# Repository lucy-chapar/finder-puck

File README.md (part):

# Finder Puck

A pocket puck so two people can find each other in a loud, crowded place without phones. Each puck has GPS, a
compass and a LoRa radio (915 MHz, no cell service needed); the two swap positions and each shows a **radar-style
arrow and the distance** to the other on a round screen. A vibration motor pulses faster as you get closer, four
LEDs on the face strobe a "beacon me" pattern for the last few metres, and there is exactly one button.

76.4 mm across, 18.3 mm thick. The body is a CNC-machined 6061 aluminium shell, black anodised, under a matte black
plastic face; between 12 and 3 o'clock the side wall is a black plastic antenna window, because aluminium would
block the radios (see [Aluminium shell and the radios](#aluminium-shell-and-the-radios)). Orange anodised
socket-cap bolts on the face pass through the PCB, a 10 mm orange button at 6 o'clock, a clear bezel around the
crystal that the four beacon LEDs light from below, and an orange index dot at 12 o'clock over the GPS patch, which
looks through a 0.9 mm skin. The back is plain anodised aluminium with the Open Source Hardware logo engraved as a
V-groove line through to bare metal; the cord goes in at the side at 6 o'clock and out of the back. The case is designed to IP55 (dust protected, water
jets from any direction) with the USB-C door slid shut and the switch plug pushed home; see [Sealing (IP55)](#sealing-ip55).
[Build guide (PDF)](docs/finder_puck_build_guide.pdf).

## Files

| Path | Contents |
|---|---|
| `finder_puck.kicad_pro` | KiCad 7 project (open this) |
| `finder_puck.kicad_sch` | Schematic ([PDF](docs/schematic.pdf)) |
| `finder_puck.kicad_pcb` | Routed 72 mm round 4-layer board (one edge notch for the battery lead) |
| `lib/finder_puck.kicad_sym`, `lib/finder_puck.pretty` | Project symbols and the 0.7 mm FPC solder footprint |
| `lib/3dmodels/` | 3D models (see "3D models" below) |
| `fab/finder_puck_gerbers.zip` | Gerbers and drill files |
| `fab/finder_puck_bom.csv`, `fab/finder_puck_cpl.csv` | Assembly BOM and placement (JLCPCB column names) |
| `mech/finder_puck.step`, `mech/finder_puck_features.json` | Populated board in 3D, and everything the case needs from it |
| `case/finder_puck_case.FCStd` | FreeCAD assembly: board, panel, crystal, battery, motor, antenna, bolts, shell, window, plate, ring, bezel, cap |
| `case/finder_puck_case.step` | All made parts in STEP |
| `case/finder_puck_{shell,window}_shop.step`, `case/finder_puck_shell_drawing.pdf` | For the shop: the shell and the window each on its own, origin on the axis at the back face, and the shell's A3 drawing (threads, tolerances, finish, setups) |
| `case/finder_puck_{window,plate,ring,bezel,cap}.stl` | Print files (`finder_puck_shell.stl` too, for previews) |
| `case/finder_puck_logo_vgroove.svg`, `case/oshw_logo.svg` | 1:1 drawing of the back logo's V-groove path for the machinist; the logo's source path (Simple Icons, CC0) |
| `case/finder_puck_gaskets.svg`, `case/finder_puck_gaskets.dxf` | 1:1 cutting template for the lid, crystal and door gaskets; the same plus the seam seal and window strip as a DXF for a converter's cutter (a layer per foam thickness) |
| `case/finder_puck_{door,switchplug}.stl` | The sliding USB-C door and the TPU switch plug |
| `docs/finder_puck_build_guide.pdf` | Step-by-step assembly guide (IKEA style) |
| `manual/` | The guide's content, renderer and layout scripts |
| `docs/finder_puck_render{,_pair,_back}.png` | Blender studio renders: the puck searching, the pair that found each other (beacons lit), the back |
| `case/export_meshes.py`, `case/render_blender.py` | Mesh export from the FreeCAD assembly, and the Blender scene behind the renders (see "Renders" below) |
| `tools/`, `case/build_case.py`, `case/render_case.py`, `regen.sh` | Generators for all of the above |
| `firmware/` | ESP32-S3 firmware (PlatformIO); see [firmware/README.md](firmware/README.md) |

## Parts

| Ref | Part | Job |
|---|---|---|
| U1 | ESP32-S3-WROOM-1-N8 | Brain; flashed over USB-C (native USB) |
| U2 | RFM95W-915S2 (SX1276) + U.FL (J4) | LoRa link between the two pucks; the feed is a single pre-routed top-layer track |
| U3 | u-blox SAM-M10Q | GPS with built-in patch antenna, under the sky window |
| U4, U5 | LIS3DH + LIS2MDL | Tilt-compensated compass |
| J3 | 1.28″ 240×240 GC9A01 round IPS panel | The radar screen (bare panel, 12-pin 0.7 mm FPC soldered to the board) |
| Q2, R13–R15 | Backlight driver | Two parallel white LEDs from the battery rail, PWM dimmed |
| LED1–LED4 | WS2812B-2020 | Beacon, up four light pipes into the translucent bezel |
| J5, Q1, D1 | Coin vibration motor and driver | Haptic pulse |
| U6, U7 | MCP73831 charger, AP2112K 3.3 V regulator | 1S LiPo on J2, charged from USB-C |
| SW1 | C&K PTS645 (5 mm stem), under the orange cap | Beacon / pair button |
| SW2, Q3, R22 | C&K PCM12 slide switch, AO3401A | On/off: the switch grounds the P-FET's gate, the FET carries the current |
| H1–H4 | M2.5 plated holes | The four case bolts pass through them |
| H5 | 2.5 mm hole | Motor lead comes up through the board |
| R21, R25, R26 | Dividers | Charger state and USB-present sensing, scaled to 3 V |
| TP1, TP2 | Test pads | UART0 TX/RX, reachable with the plate off |

ESP32 pins: LoRa SPI on IO10–IO14 (NSS, MOSI, SCK, MISO, RST), DIO0/DIO1 on IO4/IO5. GPS UART on IO17 (to GPS)
and IO18 (from GPS). I2C on IO8 (SDA) / IO9 (SCL) for LIS3DH (0x18) and LIS2MDL (0x1E). **Display on its own SPI
bus: SCK IO40, MOSI IO41, CS IO42, D/C IO21, RST IO47, backlight PWM IO48.** LEDs IO38 (through 220 Ω), motor
IO7 (IO39 has a pull-up at reset and would run the motor during boot), button IO0, battery sense IO1 (half of
VSYS), LIS3DH INT1 IO2, charger state IO6 (high only when the cell is full), USB present IO15.

The panel's FPC pinout (1–12): GND, LEDK, LEDA, VDD, GND, GND, D/C, CS, SCL, SDA, RESET, GND. Run the display at
40–80 MHz (never 26.67 or 13.33 MHz: a harmonic lands on GPS L1).

## How it goes together

Z = 0 is the top of the PCB.

- **Shell** (6061-T6, black anodised): machined in three setups, from the top, the back and the side, with no
  undercuts. A 1.8 mm floor, a bay for a 503450-class LiPo (34.5 × 52 × 5.3 mm, on 0.5 mm foam) whose wall is a
  Ø68.8 bore under the board's Ø72.8 one, so the step between them is the 2 mm ledge the board rests on; four
  Ø6.5 bosses with tapped M2.5 holes (5 mm of thread, blind) that run into the bay's wall with 1.5 mm inside radii
  (a 3 mm cutter); a pocket for the 10 mm coin motor at 2 o'clock; a slot in the bay wall at 304° for the battery
  lead and the antenna pigtail (floor to ledge, out to the board's bore, 1.5 mm inside radii); and the switch slot (1 mm corner radii) with its finger scallop (2 mm radii) and the
  switch plug's Ø1.6 pin hole, all below the rim, so the seam seal passes over them unbroken. Between 12 and 3
  o'clock (−14° to 81° at the floor) the wall is cut down to the floor for the antenna window, and the cut's two
  ends are 60° flanks, so the window gasket on them is squeezed by the bolts like the rim seal is; the boss at 45°
  stands on its own there, and the one at 315° stays whole outside it. Two Ø2.1 holes in that floor take the window's pegs. The outer edge of the back has a
  1 mm radius. The back is plain apart from the Open Source Hardware logo, 22 mm across, engraved as a line: a 90°
  V-bit follows its outline (a contour, not a pocket) 0.3 mm deep, so the groove is 0.6 mm wide, after anodising so
  it shows bare aluminium (`case/finder_puck_logo_vgroove.svg` is the 1:1 drawing). The lanyard is two Ø3.0 holes drilled square to the
  surface at 6 o'clock, one up from the back (r 35.3, stopping 1 mm above the side hole's axis, so its point stays
  0.7 mm under the boss's top) and one in from the side (Z −6.2), meeting in a boss inside the wall, with 0.4 mm countersinks on both mouths; deburr the inside of the bend.
- **Window** (black, printed): the plastic wall that fills the shell's notch, 0.6 mm clear of the notch floor and
  both flanks (normal to each face: the window gasket's squeeze), flush with the shell's rim at the top. It carries
  the 915 MHz flex antenna on its inside, the USB-C opening up to the parting line, the door's pocket with its
  sealing land and lower groove, and two feet inside the wall that stand on the shell's floor with Ø2 pegs in its
  holes, which locate it and set the gasket's squeeze.
- **Board** sits on the ledge (the 2 mm step between the two bores, cut away in the window); the motor lead comes up through H5 next to J5,
  and the battery lead and the antenna pigtail come up through a 4.5 mm notch in the board edge at 304°. J2 sits
  5.6 mm from the wall so the PH plug fits in front of it.
- **Ring** (black): a short cup standing on the board on a 0.5 mm foam ring. Its 0.85 mm wall (Ø36.3 bore,
  0.35 mm around the panel) is open at 6 o'clock where the panel's chin and the folded FPC pass, and starts
  3.6 mm up over the ESP32 can. The panel drops in from above onto the ledge 4.0 mm above the board. The ring
  is modelled 0.25 mm into the foam, so the bolted stack always preloads it. Over the GPS module (64–116°) the
  wall is a single 0.45 mm perimeter (outer face at r 18.6), 0.6 mm from the module at its widest: the SAM-M10Q
  data sheet (UBX-22013293, table 19) gives 15.4–15.6 mm over the whole height, 5.8–6.8 mm tall, with
  de-paneling tabs of up to 0.3 mm at the PCB corners. u-blox's own STEP draws the patch 0.5 mm narrower than
  the drawing does, so the drawing is what the case is built to.
- **Bezel** (clear resin): a 0.3 mm foam gasket sits on the panel's glass, the Ø37.5 × 1.0 mm flat mineral
  crystal rests on the ring's top, and the bezel sits over both: a skirt around the ring top locates it (0.25 mm
  radial), its seat holds the crystal (0.25 mm radial), its lip (Ø34.8 window, flared to Ø43.4) overlaps the
  glass by 0.2 mm and is the visible dial ring, pressing a 0.3 mm die-cut foam ring (Ø35.2–37.2) onto the
  crystal's edge, and its 0.5 mm flange under the plate skin, which runs all the way round, is what the bolts
  clamp, through a die-cut lid gasket. The flange has a lobe at 6 o'clock that carries the button bore's sleeve
  (down to Z 5.2, with a 0.4 mm lead-in, for the cap's O-ring) and a tab out to the charge LED with a Ø1.2 mm
  light pipe up through the skin to the face (Ø1.6 below the flange, 0.3 mm above the LED). Four Ø3 mm light
  pipes hang from the flange to 0.3 mm above the WS2812s, so the whole lip glows when the beacon runs. Over the
  GPS module (12 o'clock, 64–116°) the ring wall is thinned and nothing of the bezel beyond r 18.7 comes below
  the flange (Z 7.0, 0.2 mm over the tallest module). The ring used to be one part; a panel cannot be fitted past a ledge below it and a lip above it, hence the split. `LIP_PROUD`
  raises the lip's top above the face (default 0, see "Seeing the beacon from the side").
- **Plate** (black): plastic on purpose, since it is the GPS patch's radome. Skin 1.6 mm, face at Z 8.6, Ø8 bosses
  down to the board (they, not the rim, are the datum: the 1.8 mm skirt stops 0.6 mm above the rim of the shell and
  the window, the gap the 1.0 mm foam seal is squeezed into), Ø5.2
  counterbores so the orange M2.5 × 12 socket-cap heads sit 0.2 mm proud on a 0.5 mm nylon washer (Ø3.0 bores,
  Ø2.8 holes in the board), the Ø44 bezel opening (0.3 mm reveal) with a pocket 0.7 mm deep under
  the skin for the bezel's flange and the lid gasket, the skin thinned to 0.9 mm over the GPS module out to the
  wall (`GPS_WINDOW = "open"` in `build_case.py` cuts it open instead), a blind Ø1.8 × 0.6 mm hole in that cover
  at 12 o'clock for a glued orange 1.75 mm filament stub, the Ø10.6 button bore (the bezel's sleeve continues
  it), a Ø1.4 bore for the charge-LED pipe, a 1.2 mm dimple beside the switch slot marking its ON end (towards 9 o'clock, away from the
  button: the PCM12 closes terminals 1–2 with the knob at the terminal-1 end, and terminal 1 is the grounded
  one), and the 13.5 × 7.5 mm USB-C opening shared with the window at the parting line.
- **Cap** (orange): Ø10, 1.5 mm proud, 1.0 mm edge radius, a Ø12.4 flange captive 0.1 mm under the bezel's
  sleeve (so the cap goes on before the bezel), a
  groove for a 9 × 1 mm silicone O-ring that seals against the sleeve's bore (0.8 mm gland, 20 % squeeze;
  the groove's upper wall is 45° so it prints pocket down), and a square pocket that sits on the PTS645 stem
  (a dot of glue keeps it there).
- **USB-C door** (black): a 0.6 mm curved door, 16.7 mm wide, that slides 24.5° round the window in its pocket,
  flush with the wall (0.05 mm proud, three grip ribs), held by tongues in the two grooves, so it is captive
  once the plate is on. A die-cut 0.5 mm closed-cell foam frame on its inside rides 0.05 mm clear of the pocket
  floor while it slides and is squeezed to 0.3 mm (40 %) on the land when it is shut: a sliding seal that only
  compresses at the end of its travel, so it doesn't drag or wear. It slides open towards 2 o'clock; shut, the pocket's
  clockwise end stops it over the land; open uncovers the whole USB-C plug overmold.
- **Switch plug** (TPU 85A–95A): its body fills the switch slot 0.1 mm oversize, 0.14 mm clear of the knob, its
  flange lies on the scallop floor, with a grip ridge and a strap to a pin glued into the shell. Lift it to
  switch on or off.
- **Bolt path:** head → nylon washer → plate boss → PCB (plated, grounded 5.4 mm pad on both sides) → shell boss,
  tapped M2.5. The bolt engages 4.1 mm of thread (1.6 × its diameter). Hand-tighten only; aluminium hex sockets
  strip, and a smear of grease on the thread stops aluminium galling on aluminium. The bolts and index stub are in
  the FreeCAD model; the threads are modelled at their nominal 2.5 mm, so the bolts show as touching the shell.

`build_case.py` places every opening from the board's feature file and checks the eight made parts (the machined
shell and seven printed parts) against the populated board, panel, crystal, battery, motor, antenna, bolts, washers,
the seam seal, the window gasket, the O-ring, the door, crystal and lid gaskets and each other, and against proxies
for what the board model lacks: the mated battery plug (a 6.85 × 5.8 × 4.5 mm PHR-2 housing standing 2 mm out
of J2's mouth, 2.5 mm from the wall), the two battery wires and the pigtail standing side by side in the
notch, the FPC's 0.45 mm fold bump under the panel chin, a USB-C plug's 12.35 × 6.5 mm overmold and the GPS
module at its data-sheet limits (15.6 mm square, 6.8 mm tall, 0.3 mm de-paneling tabs at the PCB corners). The
result must be 0 interferences. The switch plug's 0.1 mm squeeze into its slot is designed, so it is listed as a
`squeeze` line rather than counted. The closed door is not checked against the cable-overmold proxy, since the
two are never there at once; instead the door is also built slid open and checked against the window, plate, seal
and the overmold (the `door open` lines: no overlap, and more than 1 mm from the overmold). It also lists every made-vs-other pair closer than
0.3 mm with the nearest point (the `gap` lines); today that list is exactly the designed seats and fits and
nothing else. The `rf:` lines give how close the aluminium comes to the antenna and to the GPS module, and the
`window gasket` line the length of foam strip to cut:

| Gap | Pairs |
|---|---|
| contact | board on the shell ledge, motor in its pocket, bolts in the shell's threads (modelled at the nominal diameter), the window's feet on the shell floor, antenna on the window, plate bosses on the board, washers under the bolt heads in the counterbores, the seal between the rim of the shell and window and the plate skirt, the window gasket between the shell and the window, the O-ring in the cap's groove and the bezel's sleeve, the door's gasket between the door and the land, the lid gasket between the bezel flange and the plate, the crystal gasket between the crystal and the lip, panel and crystal on the ring, bezel on the ring top, index stub on the bottom of its hole |
| 0.05 mm | the door in its pocket and its tongues in the grooves, the door over the seal's end, the window's pegs in their holes |
| 0.1 mm | cap flange under the sleeve, cap pocket over the button body, charge-LED pipe in its bore |
| 0.14 mm | switch plug over the switch knob |
| 0.2 mm | bezel over the panel (the compressed gasket), bezel over the crystal (its gasket), bezel flange over the GPS module at its tallest, USB-C plug overmold under the plate |
| 0.25 mm | bolt shanks in the plate bores, ring foot over the board (the compressed foam ring) |
| 0.3 mm | cap in the plate's bore, USB-C plug overmold in the window's opening |

Machine the shell (see "Machining the shell" below). Print the window upside down (its rim on the bed), the ring upside down (top face on the bed; slow the perimeters under its
0.85 mm ledge, and let the slicer print the single-perimeter 0.45 mm wall over the GPS arc as a thin wall), the
plate face down and the cap pocket down, the door standing on its edge, and the switch plug in TPU (85A–95A)
standing on its strap end. The
outer edges on the bed are 45° chamfers. The bezel's flange is a horizontal shelf whichever way up it goes and its fits are 0.25 mm, so
print it in clear resin (SLA); FDM needs supports under the flange and will not make clean light pipes.

### Aluminium shell and the radios

Aluminium blocks both radios, so nothing metal may sit between an antenna and the sky:

- **GPS:** the SAM-M10Q's patch looks up through the plate's 0.9 mm skin, so the plate stays plastic. The shell's
  wall comes within 0.5 mm of the module's corner at 12 o'clock (at the data sheet's limits), but its rim is at
  Z 3.0, 3.4 mm below the top of the patch, so it sits beside the module's ground, not over the patch.
- **LoRa:** the flex antenna moved from the shell's wall to the inside of the plastic window (14°–77°), raised
  2 mm so its lower edge is 2.5 mm above the aluminium floor, with 4 mm of plastic to the flank at its 12 o'clock
  end. The nearest aluminium is the bolt boss at 45°, 1.4 mm inside the antenna (the aluminium bolt and the board's
  ground plane were already about as close in the printed case).
- **Window, not slot:** a 915 MHz wave is 33 cm long; a small plastic window in a metal wall would pass very little,
  so the window is a third of the wall, open above to the plastic plate.

Nothing here has been measured. On the first pucks, compare the LoRa range and the GPS time to first fix
against a puck in the previous revision's all-plastic case (tag it, or check out the commit before this change); if the range is short, try the antenna lower or
higher on the window before anything else.

### Machining the shell

Send the shop `case/finder_puck_shell_shop.step`, `case/finder_puck_shell_drawing.pdf` and
`case/finder_puck_logo_vgroove.svg` (`case/shop_drawing.py` writes the first two from the build); quote it as 6061-T6, Type II black anodise (MIL-A-8625
Type II, class 2, about 10–15 µm), ±0.05 mm on the two bores, the bosses' faces and the flanks, ±0.1 mm elsewhere,
and with these notes:

- Three setups. Top: the two bores, the bay and its bosses, the notch and its flanks, the motor pocket, the cable
  slot, the peg holes, the M2.5 holes (tap drill Ø2.05 × 6 mm, thread 5 mm, 0.3 mm countersink). Back: the 1 mm
  outer radius, the lanyard's back hole, the logo. Side, on a 4th axis or an indexing fixture (two stations 25°
  apart, both radial): the switch slot and scallop and the plug's pin hole at 245°, the lanyard's side hole at 270°.
  Every other face is reachable straight down from the top or straight up from the back.
- The flanks are planes 60° from the floor, each through the radial line at the floor's corner, so a 60° (30° per
  side) chamfer mill on the top setup cuts each one in a single pass along that line, its point in the corner. That
  needs about 11 mm of flute: the notch is 10.9 mm deep. A ball-end 3D pass works too. Break the flanks' sharp
  (60°) edges where they meet the outside and the rim.
- Smallest tool: 2 mm (the switch slot's 1 mm corners); bosses meet the bay wall with 1.5 mm radii, and so do the
  6 mm wide cable slot's corners (a 3 mm cutter, 6.3 mm deep). Wall 1.8 mm, floor 1.8 mm; no undercuts.
- Mask the tapped holes from anodising, or chase the threads after. The seal faces (rim, notch floor, flanks) stay
  anodised: the foam seals as well on the oxide, and masking them would only add cost.
- Engrave the logo after anodising: a V-groove along its outline (contour, not pocket), 90° V-bit, tip 0.3 mm deep
  on the line, 0.6 mm wide at the surface (`case/finder_puck_logo_vgroove.svg`, centred on the case axis,
  12 o'clock up when you look at the back), so it reads as a bare aluminium line. Cut before anodising, it would come
  out black on black.
- Deburr the inside of the lanyard's bend so it does not saw the cord.

### Seeing the beacon from the side

The four WS2812s light the bezel lip from below and the lip is flush with the face, so the beacon only shows
from above ([side view](docs/case-side.png)). Three ways to show it from the side were weighed:

- **Lip standing proud** (`LIP_PROUD` in `build_case.py`, default 0): the lip's top rises 1.5–2 mm above the
  plate, a glowing clear ring visible from every direction, level with the orange cap (also 1.5 mm proud). No
  new part, no change to the board, the plate or the bolt sandwich, and the puck is no taller than it already
  is at the cap. Costs: the glass then sits 3.4 mm instead of 1.9 mm below the lip's top, so the lip's inner
  edge hides the outer 1.2 mm of the active area beyond about 19° off-axis (32° today) unless that edge gets
  a 45° chamfer, which would also catch more light; and the resin lip shares the first hit in a face-down
  drop with the cap. 1.5 mm is enough; 2 mm looks like a crown.
- **Smoke-PETG plate:** a 1.6 mm dark translucent skin would show four faint spots over the LEDs and a halo
  round the opening from above, but the plate's outer wall is 14 mm from the LEDs with the ring, the flange
  and the board in between, so nothing useful reaches the side; and the plate stops being matte black and
  ghosts the inside. Rejected.
- **Translucent band at the parting line** (a clear lap lip, or a sixth part): the same light-path problem
  plus a multi-material print or another part. Rejected.

Recommendation: `LIP_PROUD = 1.5` with the inner edge chamfered, if the beacon should be seen from the side;
the default build keeps the flush lip, so the look the owner chose is unchanged until that one constant is set.

## Sealing (IP55)

IP55 is dust protected (no harmful deposit) and water jets from any direction (IEC 60529: a 6.3 mm nozzle,
12.5 l/min from 2.5–3 m, at least 3 minutes). Every way in from outside ends at one of these:

| Path | Seal |
|---|---|
| Shell-to-plate seam | 1.0 mm closed-cell foam (EPDM, neoprene or PORON), a 1.7 mm wide ring (Ø72.9–76.3) on the rim of the shell and the window under the plate's 1.8 mm skirt, squeezed to 0.6 mm (40 %) by the bolted stack. The plate's bosses stay the datum, so the squeeze does not depend on how hard the bolts are done up. At the door it runs out to the pocket floor and the land, and it is open only across the USB-C opening itself, inside the door's gasket |
| Shell to window | a 1.0 mm closed-cell foam strip, 1.7 mm wide and about 87 mm long, along the notch floor and up both 60° flanks to the rim, where the seam seal's ring runs over its ends; squeezed to 0.6 mm normal to each face. The window's feet stand on the floor, so its squeeze is set by the parts, not by the bolts |
| USB-C opening | Sliding door: a die-cut 0.5 mm closed-cell foam frame on its inside, squeezed 40 % on a raised land round the opening when shut (and clear of the pocket while sliding) |
| Switch slot | TPU plug in the scallop; the slot no longer reaches the seam |
| Button | 9 × 1 mm silicone O-ring on the cap, in the bezel's sleeve (grease it) |
| Bolt bores | DIN 433 M2.5 nylon washer under each head; the tapped holes in the shell are blind |
| Crystal | die-cut 0.3 mm closed-cell foam ring on its edge, squeezed to 0.2 mm under the bezel's lip |
| Bezel to plate | die-cut 0.3 mm closed-cell foam lid gasket on the bezel's flange, squeezed to 0.2 mm under the plate's pocket ceiling. It rings the opening and runs round the button bore (1.5 mm web) and the charge-LED pipe (1.1 mm web), so water down either bore stops at it |
| Charge LED | a light pipe on the bezel, up through the skin: sealed by the lid gasket round it, not by a hole in the plate |
| Index stub | glued into a blind hole, 0.3 mm of skin under it |
| GPS window | the 0.9 mm skin (`GPS_WINDOW = "open"` cuts a hole and is not sealed; the build prints a CHECK) |
| Lanyard hole | two holes meeting in a solid boss, not into the case; the window's peg holes are blind and inside the seal |

Nothing is glued or potted: the lid (plate, bezel, crystal, cap) comes off as one piece with the four bolts, so
the panel stays reachable, and the gaskets are cut again from the 1:1 template `case/finder_puck_gaskets.svg`
(lid and crystal gaskets, and the door's frame flat) when they take a set. The lid gasket and the
0.5 mm foam ring under the ring are squeezed in series by the bolted stack (the plate's bosses fix the total),
so the lid gasket wants a much softer foam than the ring's (see "Sourcing the seals"); a
black crystal gasket shows as a thin dark line through the clear lip, a white or clear one does not. Nothing has been tested yet: the rating is what the design aims at. To check a built puck, put a
dry tissue inside, close it, and spray it from 2.5–3 m with a hose and a 6.3 mm nozzle (a 12.5 l/min flow)
for 3 minutes, turning it to reach every face, then open it; for dust, shake it in a bag of talc. The design
has no pressure vent: a sealed puck that goes from a hot car into cold water pulls a little vacuum, so if
water gets in only after big temperature swings, an adhesive ePTFE vent over a small hole in the floor is the
next step.

### Sourcing the seals

| Seal | Qty | Material | Where |
|---|---|---|---|
| Seam seal, window strip | 1 + 1 | 1.0 mm PORON 4701-15 Soft Seal (made for dust and water gaskets), or 1/32" (0.8 mm) closed-cell neoprene/EPDM sponge with adhesive as a stopgap (25 % squeeze instead of 40 %) | Rogers samples, or a converter (TBP Converting, Stockwell Elastomerics, JBC Technologies) |
| Door frame | 1 | 0.5 mm PORON 4701-30 Very Soft (0.53 mm supported) | converter, as above |
| Crystal gasket | 1 | 0.30 mm PORON 4701-50 Firm-Thin (about 32 psi at 25 %, ±0.08 mm thick) | converter, as above |
| Lid gasket | 1 | 0.3 mm: the softest closed-cell foam a converter has at that thickness, else 4701-50 Firm-Thin; see below | converter, as above |
| Foam ring under the ring (not a seal, but in the lid's force path) | 1 | 0.5 mm PORON 4701-50 Firm (0.51 mm) | converter, as above |
| O-ring | 1 | 9 × 1 mm silicone, 70A (RS PRO 772-044, bag of 50) | RS, TME, any metric O-ring stockist |
| Washers | 4 | DIN 433 M2.5 nylon, 2.7 × 5 × 0.5 mm | Accu, TME, Bossard, Essentra |

Converters cut from `case/finder_puck_gaskets.dxf` with a knife plotter or laser, without tooling; for two or
three pucks, the 1:1 SVG and a sharp blade do too. Adhesive: none on the lid, crystal and seam gaskets, which are
clamped; a thin acrylic PSA on the window strip and the door frame helps assembly.

**The lid stack.** The bezel stands on the ring, so the lid gasket (about 530 mm²) and the 0.5 mm foam ring under
the ring (58 mm²) carry the same bolt force in series, and share the 0.35 mm of squeeze the parts leave them. In
one foam the ring's foam, with a ninth of the area, would take nearly all of it and the lid gasket only about
0.05 mm. So the foam ring is firm PORON 4701-50 (0.51 mm), and the lid gasket is the softest 0.3 mm foam to be had.
No very soft PORON is made that thin, so the lid gasket's squeeze stays small: check it on the first puck (a strip
of paper under the gasket should be held all round once the bolts are in) and in the hose test. A 0.5 mm very soft
lid gasket in a pocket 0.2 mm deeper is the fix if it leaks. The crystal gasket is not in that chain: the crystal
sits on the ring as the bezel does, so its 0.1 mm squeeze is set by the crystal's and the bezel's thickness.

## Renders

Made in Blender 3.5 (Cycles, Metal GPU) from the FreeCAD assembly. `regen.sh` does not run this, because it takes
5 to 13 minutes a view on the M4 (the back view is the slowest):

    MESH_DIR=case/blender_mesh /Applications/FreeCAD.app/Contents/Resources/bin/freecadcmd case/export_meshes.py
    blender -b --python case/render_blender.py -- hero,pair,back 512 2400

These renders predate the aluminium shell (they show the printed case and the old debossed back); `render_blender.py`
already has the anodised shell, the bare V-groove logo, the window and the new cord route, so re-run it. The screen
graphics, the cord and the cord lock exist only in the Blender scene. Each view is also saved as
`case/blender_mesh/finder_puck_<view>.blend` for hand tweaking. The hero's rim light is placed from the camera's
mirror angle off the crystal; move that camera and the light's reflection slides onto the screen.

## 3D models

Real models now cover the parts that used to be boxes:

| Part | Model | Source and licence |
|---|---|---|
| ESP32-S3-WROOM-1 | `ESP32-S3-WROOM-1.step` | KiCad library (gitlab.com/kicad/libraries/kicad-packages3D), CC-BY-SA 4.0 with the KiCad design exception |
| SAM-M8Q/M10Q | `ublox_SAM-M8Q.step` | SparkFun KiCad libraries, CC BY 4.0 (offset to KiCad's footprint); `ref/ublox_SAM_official.step` is u-blox's own geometry for cross-checking |
| USB-C HRO TYPE-C-31-M-12 | `USB_C_Receptacle_HRO_TYPE-C-31-M-12.step` | SparkFun, CC BY 4.0 |
| WS2812B-2020 | `LED_WS2812B-2020_PLCC4_2.0x2.0mm.step` | SparkFun, CC BY 4.0 |
| PTS645 button, U.FL, passives | KiCad 7's own library | shipped with KiCad |
| RFM95W, JST PH, JST SH | generated by `tools/make_models.py` | correct outline and height, plain shapes |

Each model's position was checked by exporting a test board and measuring where the solid lands relative to its
footprint. `make_models.py` refuses to overwrite a real model.

## Checks

- Generator: the schematic netlist is checked pin by pin against the parts list; the board layout is checked for
  parts taller than 3.5 mm under the panel, parts under the folded FPC, and parts under the case bosses.
- Board: DRC must report no violations and 0 unconnected (the generator prints it). The design rules are verified
  after loading; if they are not the project's, the build stops.
- Schematic: run ERC in KiCad (Inspect → Electrical Rules Checker); KiCad 7 has no command-line ERC.
- Case: 0 mm³ interference, printed in `build_case.py`'s output, followed by the `gap` list (every made-vs-other
  pair closer than 0.3 mm, which should be the designed seats and fits only), the `rf:` lines (aluminium to the
  antenna 1.4 mm, to the GPS module 0.5 mm, both beside rather than over them) and a `mesh` line per STL (closed,
  no self-intersections).

## Before ordering

- **Nothing has been built yet.** The firmware in [`firmware/`](firmware) drives the GC9A01 and
  builds, but hasn't run on hardware. Its README lists what still needs checking on a real board.
- **Panel FPC, pin 1:** the board puts pin 1 on the 3 o'clock side after the FPC folds under the glass, derived from
  the panel drawing's front view. Buy two panels first and confirm with a loupe which face carries the contacts
  after the fold and where pin 1 lands; if it is mirrored, flip `FPC_PIN1_RIGHT` in `generate_puck.py` and
  regenerate. The FPC tail (12.24 mm) reaches the pads with about 1 mm to spare at the 4.0 mm panel height.
- **GPS footprint:** the SAM-M10Q sits on KiCad's SAM-M8Q footprint, which u-blox lists as pin-compatible.
  The panel's metal frame is closer to the module than u-blox likes (a few dB of margin); the open window compensates.
- **Battery polarity:** J2 pin 1 is `+`. Many LiPo leads are wired the other way round; check with a meter.
- **Antenna:** an adhesive flex antenna for 915 MHz no larger than 40 × 7 mm with a U.FL pigtail of at least
  100 mm (2J 2JF0515P, 39.9 × 7 mm, fits); it goes on the inside of the plastic window, never on the aluminium. Its
  cable end goes at 3 o'clock and the pigtail runs along the floor to the notch at 304° and up to J4. Always connect it to J4 before the radio transmits.
- **Factory parts:** the RFM95W is not stocked by JLCPCB (consign it or hand-solder it); the SAM-M10Q is
  (C5443880). The BOM's LCSC column is filled for everything else: the named parts, and the passives by value
  and package (Samsung MLCCs and UNI-ROYAL 1 % resistors, checked on jlcpcb.com on 2026-10-20). All are
  JLCPCB basic parts except the 150 kΩ 0402 (C25755) and the 27 Ω 0805 (C17594), which have no basic
  equivalent, and the connectors, LEDs and ICs, which are extended. The CPL adds JLCKicadTools' rotation
  corrections (SOT-23 −90°, USB-C shell 180°, WS2812B-2020 90°, JST PH 180°; its table was checked on
  2026-10-20, and the tool is deprecated in favour of JLCPCB's Fabrication Toolkit, which carries the same
  table). The JST SH (J5) is not in that table: 180° is assumed because KiCad draws both horizontal JST
  footprints the same way, so confirm it in the preview along with pin 1 of every polarised part, especially
  U2–U5. Gerbers, drills and the CPL share the drill/place origin. Order with "min via hole 0.25 mm" and edge rails; tell them the switch knob (2 mm at 245°)
  protrudes past the round outline and that the notch at 304° is intended.
- **Bolts:** M2.5 × 12 socket cap, aluminium (non-magnetic, matters for the compass 7 mm from one of them),
  into M2.5 threads tapped in the aluminium shell (no inserts). Grease the threads.
- **Shell:** machined and anodised to `case/finder_puck_case.step` with the notes in "Machining the shell". Check
  the logo is carved after anodising and the tapped holes and seal faces were masked.
- **Factory assembly:** JLCPCB's preview usually needs part rotations corrected. J3 (the panel) is soldered by
  hand; TP1/TP2 and H1–H5 are not parts. Match parts by the manufacturer numbers in the BOM.
- **Crystal:** Ø37.5 × 1.0 mm flat mineral watch crystal (sold in 0.1 mm steps); it bears on a 0.6 mm land.
- **Battery:** a 503450 cell with 28 AWG leads (the notch and the bay above the cell are sized for that); put a
  0.2 mm PET or Kapton sheet between the cell and the board.

## Shopping list

Everything the puck needs that is not on the JLCPCB-assembled board, for two pucks plus spares. Prices are rough
US dollars per unit or pack as listed on 2026-10-22, before shipping, tax and duty. Stock moves, so check it at
order time. AliExpress and Amazon listings go stale; the first column is the spec to buy against.

**Buy the panels first:** pin 1 has to be checked on a real panel (see "Before ordering") before the boards are
ordered. The rest can be ordered with the boards; the AliExpress lines take longest.

| Part (buy to this spec) | Source | Qty | ~Unit | Lead time | Check when it arrives |
|---|---|---|---|---|---|
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
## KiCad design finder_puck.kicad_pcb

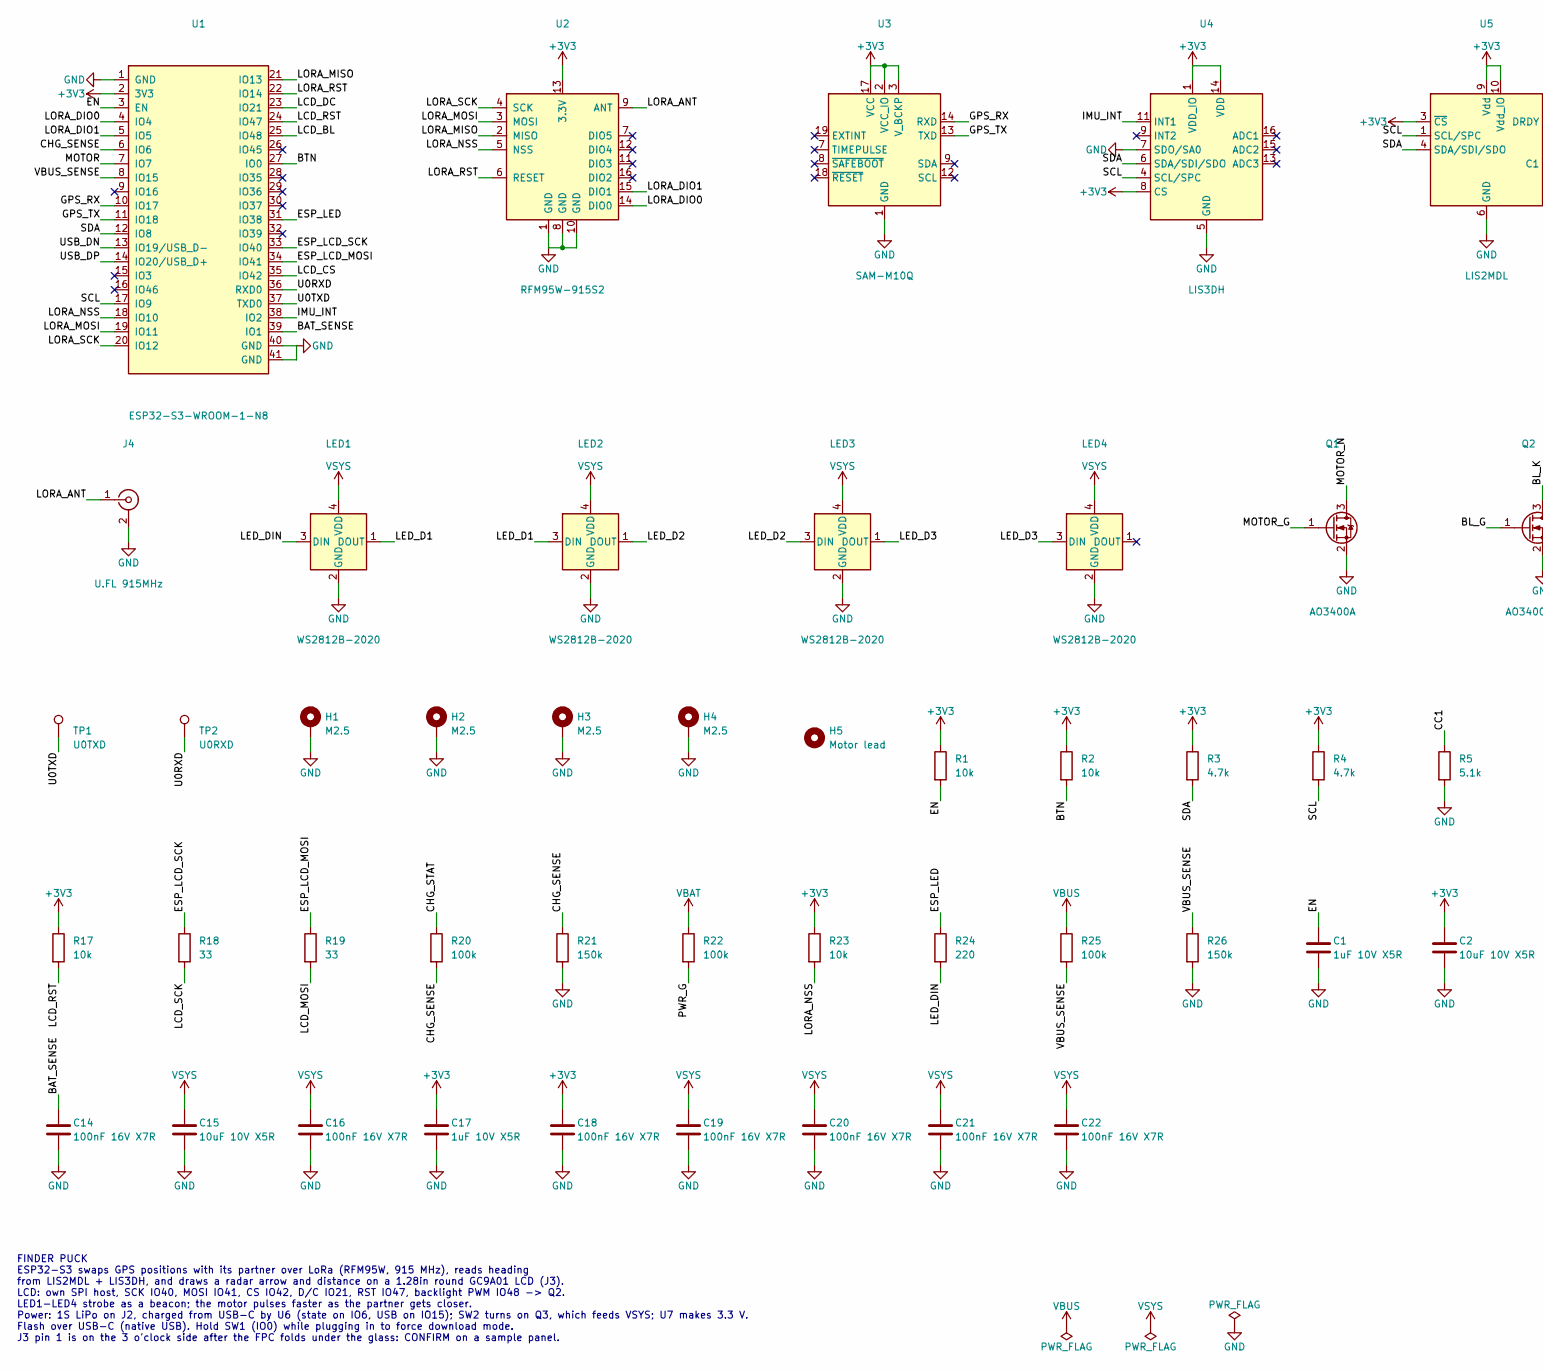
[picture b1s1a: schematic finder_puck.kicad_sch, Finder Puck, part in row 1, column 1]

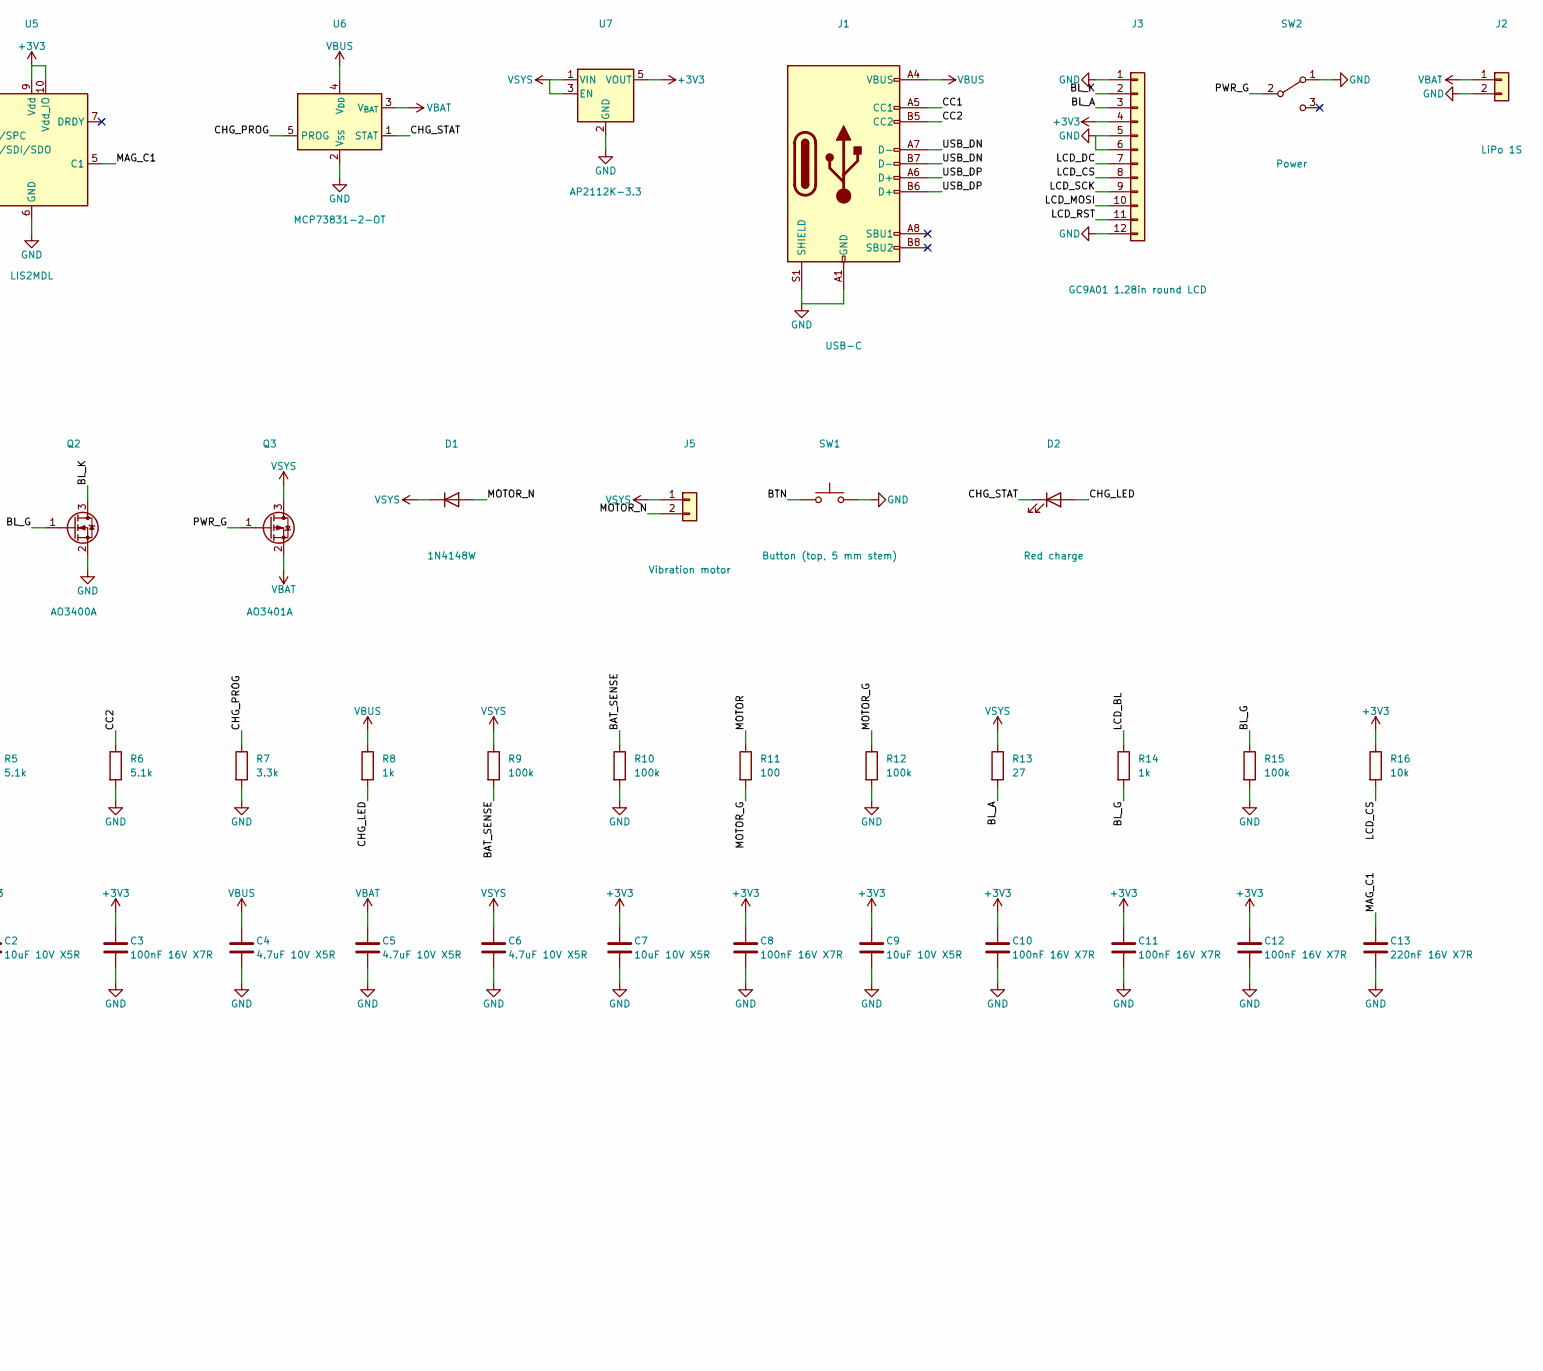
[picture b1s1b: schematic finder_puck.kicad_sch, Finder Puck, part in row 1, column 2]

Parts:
C1: 1uF 10V X5R; C_0402_1005Metric
C2, C7, C9, C15: 10uF 10V X5R; C_0805_2012Metric
C3, C8, C10, C11, C12, C14, C16, C18, C19, C20, C21, C22: 100nF 16V X7R; C_0402_1005Metric
C4, C5, C6: 4.7uF 10V X5R; C_0603_1608Metric
C13: 220nF 16V X7R; C_0402_1005Metric
C17: 1uF 10V X5R; C_0603_1608Metric
D1: 1N4148W; D_SOD-123
D2: Red charge; LED_0603_1608Metric
H1, H2, H3, H4: M2.5; MountingHole_2.7mm_M2.5_Pad
H5: Motor lead; Hole_2.5mm_NPTH
J1: USB-C; USB_C_Receptacle_HRO_TYPE-C-31-M-12
J2: LiPo 1S; JST_PH_S2B-PH-SM4-TB_1x02-1MP_P2.00mm_Horizontal
J3: GC9A01 1.28in round LCD; LCD_FPC_12P_P0.70mm_Solder
J4: U.FL 915MHz; U.FL_Hirose_U.FL-R-SMT-1_Vertical
J5: Vibration motor; JST_SH_SM02B-SRSS-TB_1x02-1MP_P1.00mm_Horizontal
LED1, LED2, LED3, LED4: WS2812B-2020; LED_WS2812B-2020_PLCC4_2.0x2.0mm
Q1, Q2: AO3400A; SOT-23
Q3: AO3401A; SOT-23
R1, R2, R16, R17, R23: 10k; R_0402_1005Metric
R3, R4: 4.7k; R_0402_1005Metric
R5, R6: 5.1k; R_0402_1005Metric
R7: 3.3k; R_0402_1005Metric
R8, R14: 1k; R_0402_1005Metric
R9, R10, R12, R15, R20, R22, R25: 100k; R_0402_1005Metric
R11: 100; R_0402_1005Metric
R13: 27; R_0805_2012Metric
R18, R19: 33; R_0402_1005Metric
R21, R26: 150k; R_0402_1005Metric
R24: 220; R_0402_1005Metric
SW1: Button (top, 5 mm stem); SW_SPST_PTS645
SW2: Power; SW_SPDT_PCM12
TP1: U0TXD; TestPoint_Pad_D1.0mm
TP2: U0RXD; TestPoint_Pad_D1.0mm
U1: ESP32-S3-WROOM-1-N8; ESP32-S3-WROOM-1
U2: RFM95W-915S2; HOPERF_RFM9XW_SMD
U3: SAM-M10Q; ublox_SAM-M8Q
U4: LIS3DH; LGA-16_3x3mm_P0.5mm_LayoutBorder3x5y
U5: LIS2MDL; LGA-12_2x2mm_P0.5mm
U6: MCP73831-2-OT; SOT-23-5
U7: AP2112K-3.3; SOT-23-5

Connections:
+3V3: C2.1, C3.1, C7.1, C8.1, C9.1, C10.1, C11.1, C12.1, C17.1, C18.1, J3.4, R1.1, R2.1, R3.1, R4.1, R16.1, R17.1, R23.1, U1.2 (3V3), U2.13 (3.3V), U3.2 (VCC_IO), U3.3 (V_BCKP), U3.17 (VCC), U4.1 (VDD_IO), U4.8 (CS), U4.14 (VDD), U5.3 (~CS), U5.9 (Vdd), U5.10 (Vdd_IO), U7.5 (VOUT)
/BAT_SENSE: C14.1, R9.2, R10.1, U1.39 (IO1)
/BL_A: J3.3, R13.2
/BL_G: Q2.1 (G), R14.2, R15.1
/BL_K: J3.2, Q2.3 (D)
/BTN: R2.2, SW1.1, U1.27 (IO0)
/CC1: J1.A5 (CC1), R5.1
/CC2: J1.B5 (CC2), R6.1
/CHG_LED: D2.2 (A), R8.2
/CHG_PROG: R7.1, U6.5 (PROG)
/CHG_SENSE: R20.2, R21.1, U1.6 (IO6)
/CHG_STAT: D2.1 (K), R20.1, U6.1 (STAT)
/EN: C1.1, R1.2, U1.3 (EN)
/ESP_LCD_MOSI: R19.1, U1.34 (IO41)
/ESP_LCD_SCK: R18.1, U1.33 (IO40)
/ESP_LED: R24.1, U1.31 (IO38)
/GPS_RX: U1.10 (IO17), U3.14 (RXD)
/GPS_TX: U1.11 (IO18), U3.13 (TXD)
/IMU_INT: U1.38 (IO2), U4.11 (INT1)
/LCD_BL: R14.1, U1.25 (IO48)
/LCD_CS: J3.8, R16.2, U1.35 (IO42)
/LCD_DC: J3.7, U1.23 (IO21)
/LCD_MOSI: J3.10, R19.2
/LCD_RST: J3.11, R17.2, U1.24 (IO47)
/LCD_SCK: J3.9, R18.2
/LED_D1: LED1.1 (DOUT), LED2.3 (DIN)
/LED_D2: LED2.1 (DOUT), LED3.3 (DIN)
/LED_D3: LED3.1 (DOUT), LED4.3 (DIN)
/LED_DIN: LED1.3 (DIN), R24.2
/LORA_ANT: J4.1 (In), U2.9 (ANT)
/LORA_DIO0: U1.4 (IO4), U2.14 (DIO0)
/LORA_DIO1: U1.5 (IO5), U2.15 (DIO1)
/LORA_MISO: U1.21 (IO13), U2.2 (MISO)
/LORA_MOSI: U1.19 (IO11), U2.3 (MOSI)
/LORA_NSS: R23.2, U1.18 (IO10), U2.5 (NSS)
/LORA_RST: U1.22 (IO14), U2.6 (RESET)
/LORA_SCK: U1.20 (IO12), U2.4 (SCK)
/MAG_C1: C13.1, U5.5 (C1)
/MOTOR: R11.1, U1.7 (IO7)
/MOTOR_G: Q1.1 (G), R11.2, R12.1
/MOTOR_N: D1.2 (A), J5.2, Q1.3 (D)
/PWR_G: Q3.1 (G), R22.2, SW2.2 (B)
/SCL: R4.2, U1.17 (IO9), U4.4 (SCL/SPC), U5.1 (SCL/SPC)
/SDA: R3.2, U1.12 (IO8), U4.6 (SDA/SDI/SDO), U5.4 (SDA/SDI/SDO)
/U0RXD: TP2.1, U1.36 (RXD0)
/U0TXD: TP1.1, U1.37 (TXD0)
/USB_DN: J1.A7 (D-), J1.B7 (D-), U1.13 (IO19/USB_D-)
/USB_DP: J1.A6 (D+), J1.B6 (D+), U1.14 (IO20/USB_D+)
/VBUS_SENSE: R25.2, R26.1, U1.8 (IO15)
GND: C1.2, C2.2, C3.2, C4.2, C5.2, C6.2, C7.2, C8.2, C9.2, C10.2, C11.2, C12.2, C13.2, C14.2, C15.2, C16.2, C17.2, C18.2, C19.2, C20.2, C21.2, C22.2, H1.1, H2.1, H3.1, H4.1, J1.A1 (GND), J1.A12 (GND), J1.B1 (GND), J1.B12 (GND), J1.S1 (SHIELD), J2.2, J3.1, J3.5, J3.6, J3.12, J4.2 (Ext), LED1.2 (GND), LED2.2 (GND), LED3.2 (GND), LED4.2 (GND), Q1.2 (S), Q2.2 (S), R5.2, R6.2, R7.2, R10.2, R12.2, R15.2, R21.2, R26.2, SW1.2, SW2.1 (A), U1.1 (GND), U1.40 (GND), U1.41 (GND), U2.1 (GND), U2.8 (GND), U2.10 (GND), U3.1 (GND), U3.4 (GND), U3.5 (GND), U3.6 (GND), U3.10 (GND), U3.11 (GND), U3.15 (GND), U3.16 (GND), U3.20 (GND), U4.5 (GND), U4.7 (SDO/SA0), U4.10 (GND), U4.12 (GND), U5.6 (GND), U5.8 (GND), U6.2 (V_{SS}), U7.2 (GND)
VBAT: C5.1, J2.1, Q3.2 (S), R22.1, U6.3 (V_{BAT})
VBUS: C4.1, J1.A4 (VBUS), J1.A9 (VBUS), J1.B4 (VBUS), J1.B9 (VBUS), R8.1, R25.1, U6.4 (V_{DD})
VSYS: C6.1, C15.1, C16.1, C19.1, C20.1, C21.1, C22.1, D1.1 (K), J5.1, LED1.4 (VDD), LED2.4 (VDD), LED3.4 (VDD), LED4.4 (VDD), Q3.3 (D), R9.1, R13.1, U7.1 (VIN), U7.3 (EN)

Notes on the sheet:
FINDER PUCK ESP32-S3 swaps GPS positions with its partner over LoRa (RFM95W, 915 MHz), reads heading from LIS2MDL + LIS3DH, and draws a radar arrow and distance on a 1.28in round GC9A01 LCD (J3). LCD: own SPI host, SCK IO40, MOSI IO41, CS IO42, D/C IO21, RST IO47, backlight PWM IO48 -> Q2. LED1-LED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

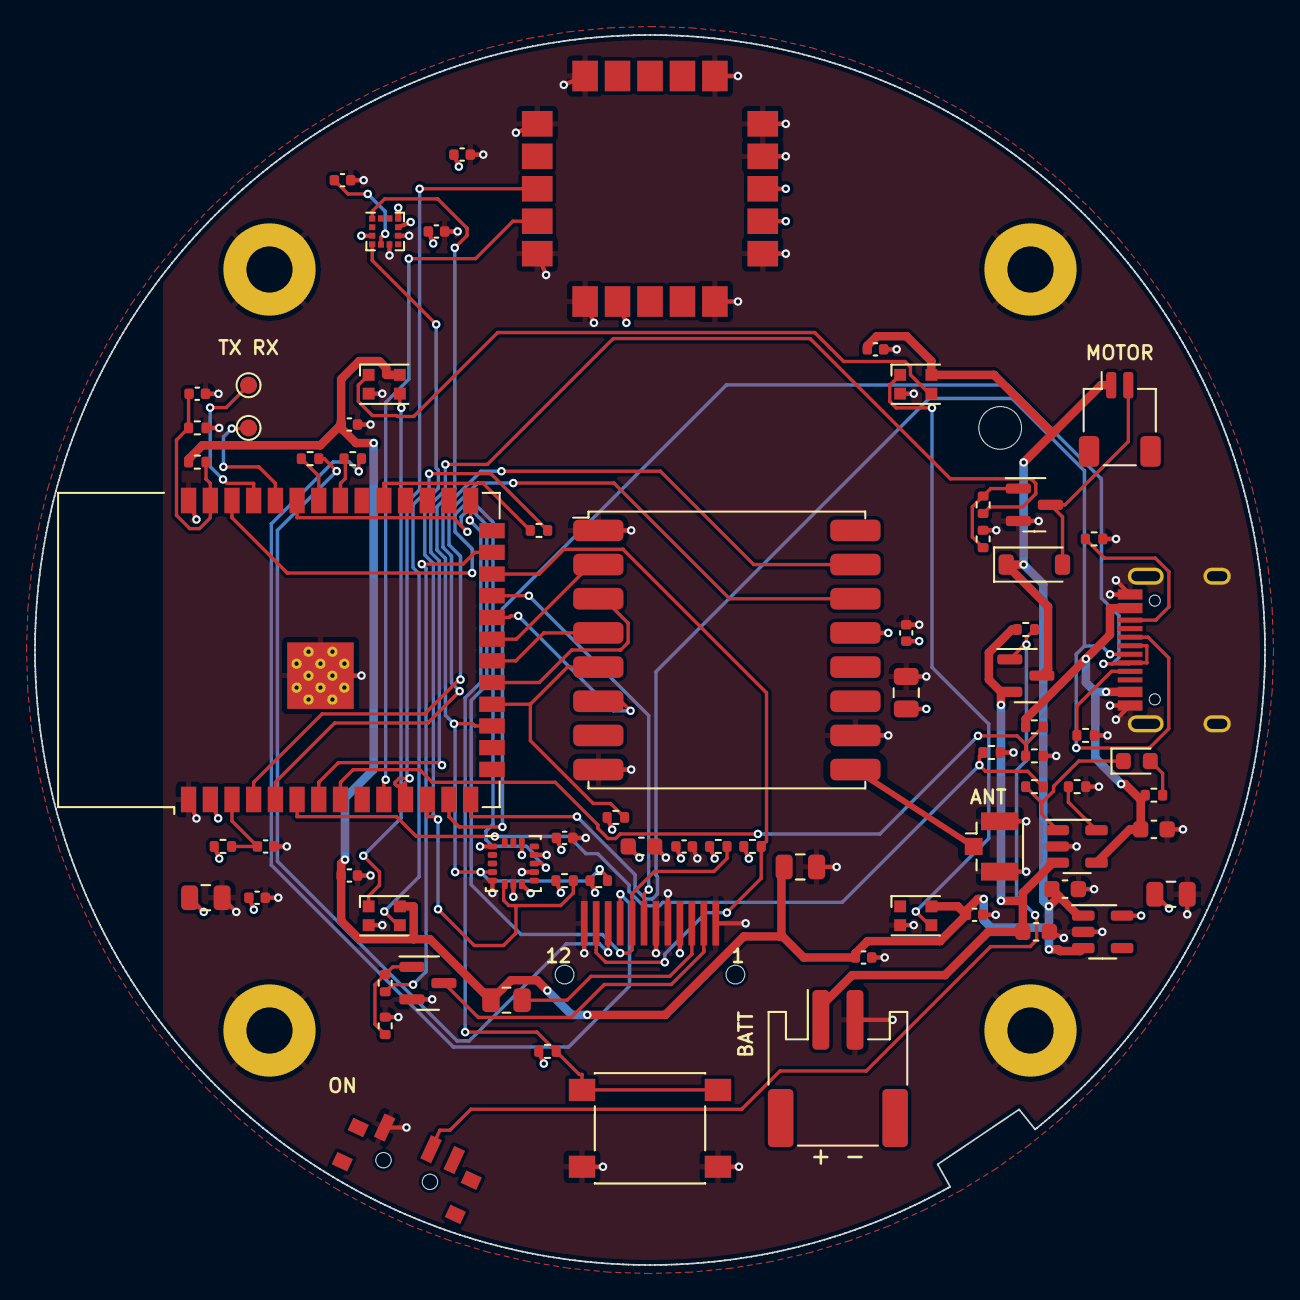
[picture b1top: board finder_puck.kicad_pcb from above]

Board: 4 copper layers, 72.0 x 72.0 mm, 78 parts (0 on the bottom side), 53 nets.

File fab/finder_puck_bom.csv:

Comment,Designator,Footprint,Quantity,Manufacturer part,LCSC Part #
1uF 10V X5R,C1,C_0402_1005Metric,1,Samsung CL05A105KA5NQNC (25 V),C52923
220nF 16V X7R,C13,C_0402_1005Metric,1,Samsung CL05B224KO5NNNC,C16772
1uF 10V X5R,C17,C_0603_1608Metric,1,Samsung CL10A105KB8NNNC (50 V),C15849
10uF 10V X5R,"C2,C7,C9,C15",C_0805_2012Metric,4,Samsung CL21A106KAYNNNE (25 V),C15850
100nF 16V X7R,"C3,C8,C10,C11,C12,C14,C16,C18,C19,C20,C21,C22",C_0402_1005Metric,12,Samsung CL05B104KO5NNNC,C1525
4.7uF 10V X5R,"C4,C5,C6",C_0603_1608Metric,3,Samsung CL10A475KO8NNNC (16 V),C19666
1N4148W,D1,D_SOD-123,1,1N4148W,C81598
Red charge,D2,LED_0603_1608Metric,1,Hubei KENTO KT-0603R,C2286
USB-C,J1,USB_C_Receptacle_HRO_TYPE-C-31-M-12,1,HRO TYPE-C-31-M-12,C165948
LiPo 1S,J2,JST_PH_S2B-PH-SM4-TB_1x02-1MP_P2.00mm_Horizontal,1,JST S2B-PH-SM4-TB,C295747
U.FL 915MHz,J4,U.FL_Hirose_U.FL-R-SMT-1_Vertical,1,Hirose U.FL-R-SMT-1(10),C88373
Vibration motor,J5,JST_SH_SM02B-SRSS-TB_1x02-1MP_P1.00mm_Horizontal,1,JST SM02B-SRSS-TB,C160402
WS2812B-2020,"LED1,LED2,LED3,LED4",LED_WS2812B-2020_PLCC4_2.0x2.0mm,4,Worldsemi WS2812B-2020-V6,C52917434
AO3400A,"Q1,Q2",SOT-23,2,AOS AO3400A,C20917
AO3401A,Q3,SOT-23,1,AOS AO3401A,C15127
10k,"R1,R2,R16,R17,R23",R_0402_1005Metric,5,UNI-ROYAL 0402WGF1002TCE,C25744
100,R11,R_0402_1005Metric,1,UNI-ROYAL 0402WGF1000TCE,C25076
27,R13,R_0805_2012Metric,1,UNI-ROYAL 0805W8F270JT5E,C17594
33,"R18,R19",R_0402_1005Metric,2,UNI-ROYAL 0402WGF330JTCE,C25105
150k,"R21,R26",R_0402_1005Metric,2,UNI-ROYAL 0402WGF1503TCE,C25755
220,R24,R_0402_1005Metric,1,UNI-ROYAL 0402WGF2200TCE,C25091
4.7k,"R3,R4",R_0402_1005Metric,2,UNI-ROYAL 0402WGF4701TCE,C25900
5.1k,"R5,R6",R_0402_1005Metric,2,UNI-ROYAL 0402WGF5101TCE,C25905
3.3k,R7,R_0402_1005Metric,1,UNI-ROYAL 0402WGF3301TCE,C25890
1k,"R8,R14",R_0402_1005Metric,2,UNI-ROYAL 0402WGF1001TCE,C11702
100k,"R9,R10,R12,R15,R20,R22,R25",R_0402_1005Metric,7,UNI-ROYAL 0402WGF1003TCE,C25741
"Button (top, 5 mm stem)",SW1,SW_SPST_PTS645,1,C&K PTS645SL50SMTR92LFS,C221877
Power,SW2,SW_SPDT_PCM12,1,C&K PCM12SMTR,C221841
ESP32-S3-WROOM-1-N8,U1,ESP32-S3-WROOM-1,1,Espressif ESP32-S3-WROOM-1-N8,C2913198
RFM95W-915S2,U2,HOPERF_RFM9XW_SMD,1,HopeRF RFM95W-915S2,
SAM-M10Q,U3,ublox_SAM-M8Q,1,u-blox SAM-M10Q-00B,C5443880
LIS3DH,U4,LGA-16_3x3mm_P0.5mm_LayoutBorder3x5y,1,ST LIS3DHTR,C15134
LIS2MDL,U5,LGA-12_2x2mm_P0.5mm,1,ST LIS2MDLTR,C919695
MCP73831-2-OT,U6,SOT-23-5,1,Microchip MCP73831T-2ACI/OT,C424093
AP2112K-3.3,U7,SOT-23-5,1,Diodes AP2112K-3.3TRG1,C51118

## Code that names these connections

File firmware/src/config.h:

#pragma once

// ---- Pins (tools/generate_puck.py, PARTS) -------------------------------
#define PIN_LORA_NSS 10
#define PIN_LORA_MOSI 11
#define PIN_LORA_SCK 12
#define PIN_LORA_MISO 13
#define PIN_LORA_RST 14
#define PIN_LORA_DIO0 4
#define PIN_LORA_DIO1 5
#define PIN_GPS_TX 17      // ESP32 -> GPS RXD
#define PIN_GPS_RX 18      // GPS TXD -> ESP32
#define PIN_SDA 8          // LIS3DH + LIS2MDL
#define PIN_SCL 9
#define PIN_IMU_INT 2      // LIS3DH INT1 (not used yet)
#define PIN_LEDS 38        // LED1-LED4 DIN
#define PIN_MOTOR 7        // AO3400A gate, high = motor on (IO39 has a reset pull-up: never use it for a load)
#define PIN_BUTTON 0       // SW1 to GND, 10k pull-up (also the boot button)
#define PIN_BATTERY 1      // VSYS through a 100k/100k divider
#define PIN_CHG_SENSE 6    // MCP73831 STAT through 100k/150k (R20/R21): high only when the cell is full
#define PIN_VBUS_SENSE 15  // VBUS through 100k/150k (R25/R26): high when USB is plugged in

// Round 240x240 GC9A01 LCD on its own SPI host (SPI3, through the GPIO matrix)
#define PIN_LCD_SCK 40
#define PIN_LCD_MOSI 41
#define PIN_LCD_CS 42      // 10k pull-up
#define PIN_LCD_DC 21
#define PIN_LCD_RST 47     // 10k pull-up
#define PIN_LCD_BL 48      // PWM to the backlight MOSFET; dark until driven

#define LED_COUNT 4
#define GPS_BAUD 9600      // SAM-M10Q factory default, NMEA

// ---- Radio ---------------------------------------------------------------------
// 915 MHz, SF9 / 125 kHz: about 200 ms on air per position packet and roughly
// 1-2 km range in a crowd with small antennas.  Check your local rules before
// changing frequency or power (US: 902-928 MHz ISM).
#define LORA_FREQ_MHZ 915.0
#define LORA_BW_KHZ 125.0
#define LORA_SF 9
#define LORA_CR 7          // 4/7
#define LORA_SYNC_WORD 0x12
#define LORA_POWER_DBM 17
#define SEND_INTERVAL_MS 1500   // plus or minus SEND_JITTER_MS so the two pucks don't keep colliding
#define SEND_JITTER_MS 300

// ---- Behaviour -----------------------------------------------------------------
#define PARTNER_LOST_MS 20000UL       // no packet for this long = "lost partner"
#define BEACON_DISTANCE_M 10.0        // strobe automatically when closer than this
#define BEACON_RSSI_DBM -55           // ...or, without GPS, when the signal is this strong
#define BEACON_BUTTON_MS 60000UL      // a button press keeps both beacons on this long
#define HAPTIC_MAX_DISTANCE_M 300.0   // no vibration further away than this
#define HAPTIC_SLOW_MS 4000           // pulse period at HAPTIC_MAX_DISTANCE_M
#define HAPTIC_FAST_MS 350            // pulse period at 5 m and closer
#define HAPTIC_PULSE_MS 70
#define PAIRING_TIMEOUT_MS 30000UL
#define PAIRING_MIN_RSSI_DBM -75      // pairing only accepts a puck that's right next to this one

// Button timings
#define LONG_PRESS_MS 2000            // release after 2 s = pairing mode
#define CAL_PRESS_MS 5000             // release after 5 s = compass calibration
#define DOUBLE_CLICK_MS 350           // two quick presses = vibration on/off

// ---- Display -------------------------------------------------------------------
// Which way up the picture is drawn (LovyanGFX setRotation, 0-3 quarter turns;
// sets the GC9A01 MADCTL).  12 o'clock on screen must be the GPS / sky-window side
// of the puck (the panel's FPC leaves at 6 o'clock).  UNVERIFIED: 0 assumes the
// panel's native top is opposite its FPC, as on most GC9A01 modules.
#define LCD_ROTATION 0
// SPI clock.  40 MHz is safe through the GPIO matrix; try 80 MHz once a board
// works.  Never 26.67 or 13.33 MHz: their harmonics land on GPS L1 (1575.42 MHz).
#define LCD_SPI_HZ 40000000
#define LCD_BRIGHTNESS 60        // backlight 0-255; dim by default, it's the biggest power draw
#define DISPLAY_FPS 8

// Pocket mode: backlight off and panel asleep when face-down or still.
#define FACE_DOWN_MS 1500        // screen down (Z < -0.6 g) this long
#define STILL_MS 60000UL         // no movement this long
#define MOTION_G 0.06            // change in acceleration that counts as movement

// ---- Compass -------------------------------------------------------------------
// Magnetic declination at the venue in degrees, east positive (look it up at
// https://www.ngdc.noaa.gov/geomag/calculators/magcalc.shtml).  Without it the
// arrow is off by that many degrees.  The bearing to the partner is from GPS,
// so it's relative to true north.
#define MAG_DECLINATION_DEG 0.0

// How each sensor's axes line up with the board.  Board frame: +X towards the
// right edge of the screen, +Y towards the top of the screen (the way the arrow
// points when the partner is straight ahead), +Z out of the screen.
// Entry i says which sensor axis (0=x 1=y 2=z) gives board axis i, and its sign.
// UNVERIFIED: check with the 'r' serial command once a board exists (README).
#define ACCEL_AXIS {0, 1, 2}
#define ACCEL_SIGN {1, 1, 1}
#define MAG_AXIS {0, 1, 2}
#define MAG_SIGN {1, 1, 1}

#define CAL_MIN_MS 15000          // figure-eight for at least this long
#define CAL_MAX_MS 45000
#define CAL_MIN_SPAN_UT 40.0      // each axis must swing at least this far (Earth's field is 25-65 uT)

// ---- Battery (1S LiPo, measured on VSYS) -----------------------------------------
#define BATTERY_DIVIDER 2.0
#define BATTERY_LOW_V 3.50        // warning icon
#define BATTERY_CRITICAL_V 3.35   // full-screen warning, beacon LEDs disabled
// Charging = USB present (IO15 high) and STAT low (IO6 low); full = both high.
